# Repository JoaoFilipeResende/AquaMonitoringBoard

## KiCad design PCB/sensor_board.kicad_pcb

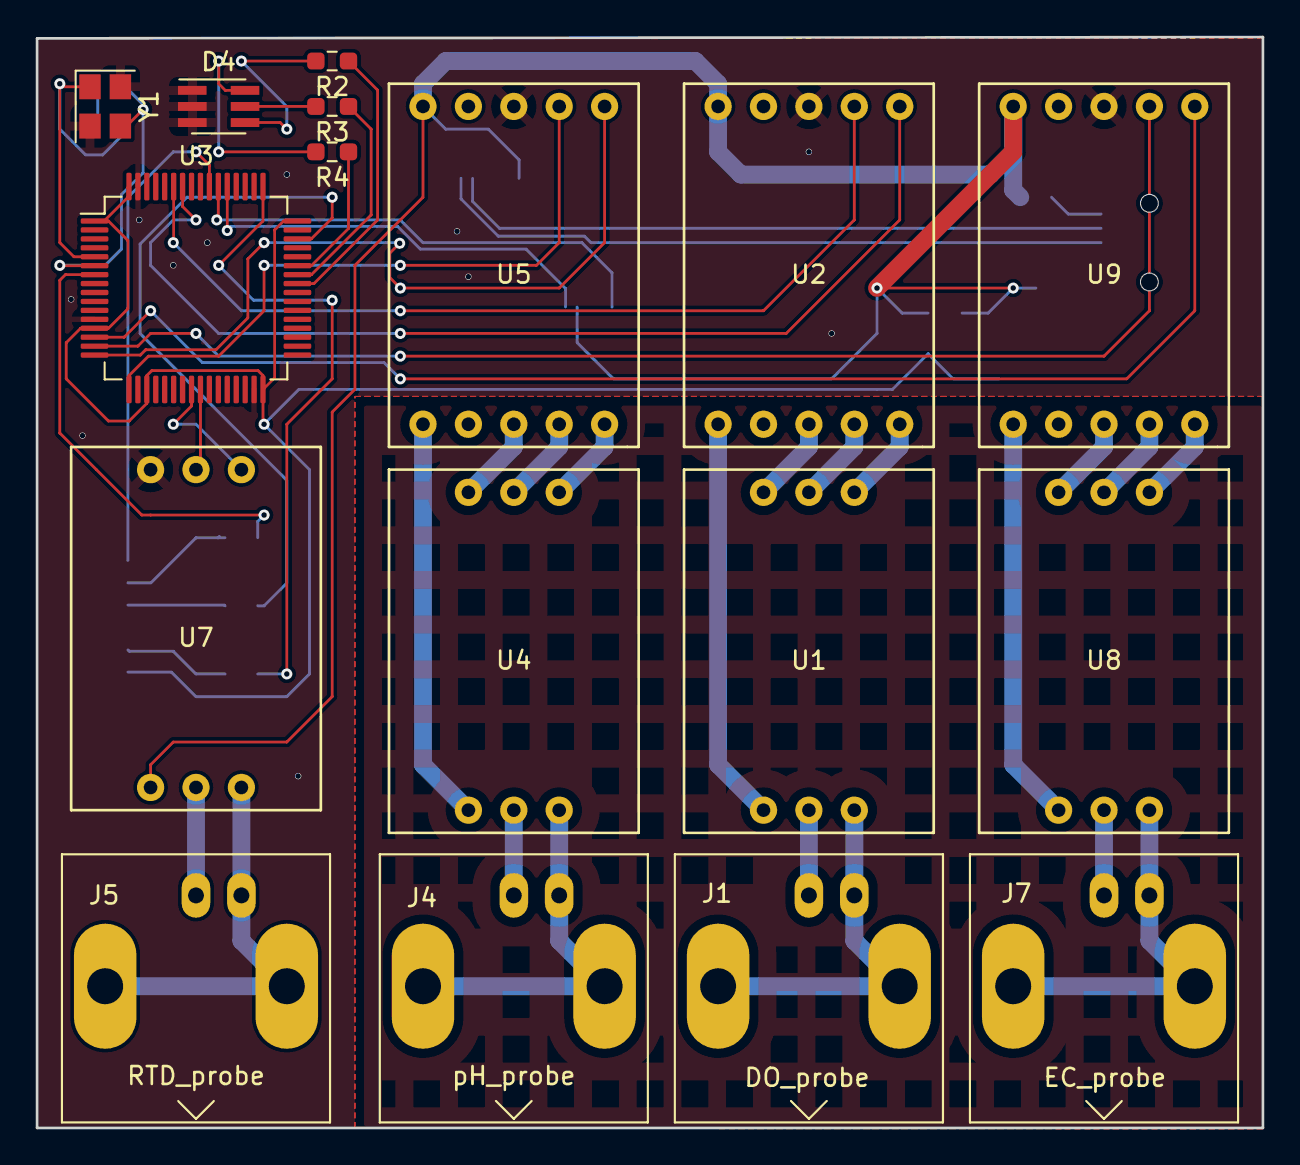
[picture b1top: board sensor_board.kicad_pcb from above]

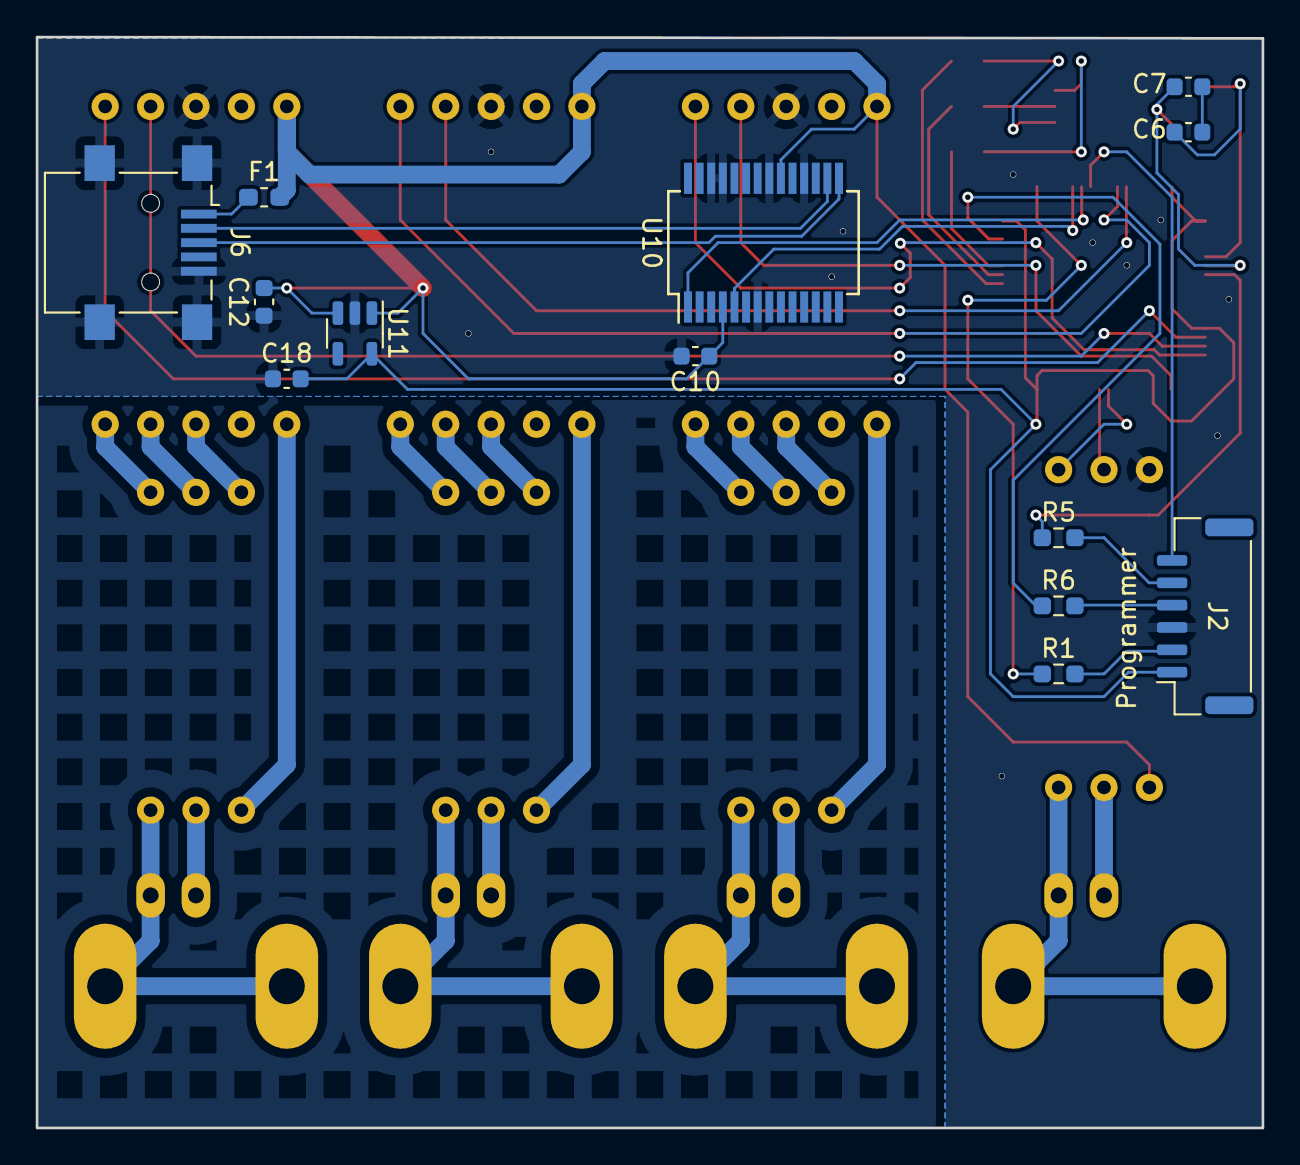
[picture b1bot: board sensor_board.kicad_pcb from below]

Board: 2 copper layers, 68.6 x 61.0 mm, 30 parts (13 on the bottom side), 52 nets.

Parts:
C6, C7: 10pF,16V; C_0603_1608Metric
C10: 100nF; C_0603_1608Metric
C12, C18: 1uF,16V; C_0603_1608Metric
D4: ASMT-YTB7-0AA02; LED_Avago_PLCC6_3x2.8mm
F1: 500 mA; Fuse_0603_1608Metric_Pad1.05x0.95mm_HandSolder
J1: DO_probe; BNC_Amphenol_B6252HB-NPP3G-50_Horizontal
J2: Conn_01x06; JST_GH_SM06B-GHS-TB_1x06-1MP_P1.25mm_Horizontal
J4: pH_probe; BNC_Amphenol_B6252HB-NPP3G-50_Horizontal
J5: RTD_probe; BNC_Amphenol_B6252HB-NPP3G-50_Horizontal
J6: USB_OTG; USB_Mini-B_Lumberg_2486_01_Horizontal
J7: EC_probe; BNC_Amphenol_B6252HB-NPP3G-50_Horizontal
R1, R2, R3, R4, R5, R6: 22; R_0603_1608Metric_Pad0.98x0.95mm_HandSolder
U1: EZO_DO; EZO_circuit
U2: Isolator_DO; EZO_voltage_isolator
U3: STM32F091RCTx; LQFP-64_10x10mm_P0.5mm
U4: EZO_PH; EZO_circuit
U5: Isolator_PH; EZO_voltage_isolator
U7: EZO_RTD; EZO_circuit
U8: EZO_EC; EZO_circuit
U9: Isolator_EC; EZO_voltage_isolator
U10: FT232RL; SSOP-28_5.3x10.2mm_P0.65mm
U11: TLV755P; SOT-23-5
Y1: 12MHz; Crystal_SMD_Abracon_ABM8G-4Pin_3.2x2.5mm

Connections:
+3.3V: C18.2, J2.1, U3.1 (VBAT), U3.13 (VDDA), U3.19 (VDD), U3.32 (VDD), U3.48 (VDDIO2), U3.64 (VDD), U11.5 (OUT)
+5V: C10.1, C12.2, F1.2, U2.5 (VCC), U5.5 (VCC), U7.6 (VCC), U9.5 (VCC), U10.4 (VCCIO), U10.20 (VCC), U11.1 (IN), U11.3 (EN)
/ISO_GND_DO: U1.3 (GND), U2.8 (GND)
/ISO_GND_EC: U8.3 (GND), U9.8 (GND)
/ISO_GND_pH: U4.3 (GND), U5.8 (GND)
/ISO_USART1_RX: U1.2 (TX), U2.7 (A)
/ISO_USART1_TX: U1.1 (RX), U2.6 (B)
/ISO_USART2_RX: U4.2 (TX), U5.7 (A)
/ISO_USART2_TX: U4.1 (RX), U5.6 (B)
/ISO_USART4_RX: U8.2 (TX), U9.7 (A)
/ISO_USART4_TX: U8.1 (RX), U9.6 (B)
/ISO_VCC_DO: U1.6 (VCC), U2.10 (VCC)
/ISO_VCC_EC: U8.6 (VCC), U9.10 (VCC)
/ISO_VCC_pH: U4.6 (VCC), U5.10 (VCC)
/LED_B_TIM1_CH3: R4.1, U3.43 (PA10)
/LED_G_TIM1_CH2: R3.1, U3.42 (PA9)
/LED_R_TIM1_CH1: R2.1, U3.41 (PA8)
/NRST: R5.1, U3.7 (NRST)
/SWCLK: R1.1, U3.49 (PA14)
/SWDIO: R6.1, U3.46 (PA13)
/SWO: J2.6, U3.55 (PB3)
/USART1_RX_DO: U2.2 (A), U3.59 (PB7)
/USART1_TX_DO: U2.1 (B), U3.58 (PB6)
/USART2_RX_pH: U3.17 (PA3), U5.2 (A)
/USART2_TX_pH: U3.16 (PA2), U5.1 (B)
/USART3_RX_RTD: U3.25 (PC5), U7.2 (TX)
/USART3_TX_RTD: U3.24 (PC4), U7.1 (RX)
/USART4_RX_EC: U3.15 (PA1), U9.2 (A)
/USART4_TX_EC: U3.14 (PA0), U9.1 (B)
/USART5_RX_COM1: U3.54 (PD2), U10.1 (TXD)
/USART5_TX_COM1: U3.53 (PC12), U10.5 (RXD)
Earth: C10.2, C12.1, C18.1, D4.1 (KB), D4.2 (KG), D4.3 (KR), J2.3, J6.5 (GND), J6.6 (Shield), U2.3 (GND), U3.12 (VSSA), U3.18 (VSS), U3.31 (VSS), U3.47 (VSS), U3.63 (VSS), U5.3 (GND), U7.3 (GND), U9.3 (GND), U10.7 (GND), U10.18 (GND), U10.21 (GND), U10.25 (AGND), U10.26 (TEST), U11.2 (GND), Y1.2, Y1.4
unnamed: C6.2, C7.1
unnamed: D4.6 (AB), R4.2
unnamed: D4.5 (AG), R3.2
unnamed: D4.4 (AR), R2.2
unnamed: J1.2 (Ext), U1.4 (PGND)
unnamed: J1.1 (In), U1.5 (PRB)
unnamed: J2.2, R1.2
unnamed: J2.4, R6.2
unnamed: J2.5, R5.2
unnamed: J4.2 (Ext), U4.4 (PGND)
unnamed: J4.1 (In), U4.5 (PRB)
unnamed: J5.2 (Ext), U7.4 (PGND)
unnamed: J5.1 (In), U7.5 (PRB)
unnamed: J6.3 (D+), U10.15 (USBD+)
unnamed: J6.2 (D-), U10.16 (USBD-)
unnamed: F1.1, J6.1 (VBUS)
unnamed: J7.2 (Ext), U8.4 (PGND)
unnamed: J7.1 (In), U8.5 (PRB)
unnamed: C6.1, U3.5 (PF0), Y1.1
unnamed: C7.2, U3.6 (PF1), Y1.3

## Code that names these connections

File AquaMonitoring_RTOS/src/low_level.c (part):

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
	xSemaphoreMutex_USART = xSemaphoreCreateMutex();

	initUSART1();  /* O.D  (PB6 -> TX / PB7 -> RX) */
	initUSART2();  /* pH   (PA2 -> TX / PA3 -> RX) */
	initUSART3();  /* RTD (PC4 -> TX / PC5 -> RX) */
	initUSART4();  /* EC   (PA0 -> TX / PA1 -> RX) */
	initUSART5();  /* PC   (PC12 -> TX / PD2 -> RX) */

}

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    }
}

static void initUSART1 (void)/* O.D  (PB6 -> TX / PB7 -> RX) */
{
	xQueueUSART1_RX = xQueueCreate( QUEUE_SIZE, sizeof( char ) );
	xQueueUSART1_TX = xQueueCreate( QUEUE_SIZE, sizeof( char ) );
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	NVIC_Init(&NVIC_InitStructure);
 }

static void initUSART2 (void)/* pH   (PA2 -> TX / PA3 -> RX) */
{
	xQueueUSART2_RX = xQueueCreate( QUEUE_SIZE, sizeof( char ) );
	xQueueUSART2_TX = xQueueCreate( QUEUE_SIZE, sizeof( char ) );
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	NVIC_Init(&NVIC_InitStructure);
 }

static void initUSART3 (void)/* Temp (PC4 -> TX / PC5 -> RX) */
{
	xQueueUSART3_RX = xQueueCreate( QUEUE_SIZE, sizeof( char ) );
	xQueueUSART3_TX = xQueueCreate( QUEUE_SIZE, sizeof( char ) );
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	NVIC_Init(&NVIC_InitStructure);
 }

static void initUSART4 (void)	/* EC (PA0 -> TX / PA1 -> RX) */
{
	xQueueUSART4_RX = xQueueCreate( QUEUE_SIZE, sizeof( char ) );
	xQueueUSART4_TX = xQueueCreate( QUEUE_SIZE, sizeof( char ) );
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 }


static void initUSART5 (void)/* PC   (PC12 -> TX / PD2 -> RX) */
{
	xQueueUSART5_RX = xQueueCreate( QUEUE_SIZE, sizeof( char ) );
	xQueueUSART5_TX = xQueueCreate( QUEUE_SIZE, sizeof( char ) );
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
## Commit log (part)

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2023-07-09 add project software
